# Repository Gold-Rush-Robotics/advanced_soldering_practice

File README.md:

# advanced_soldering_practice
Advanced Soldering Practice PCB

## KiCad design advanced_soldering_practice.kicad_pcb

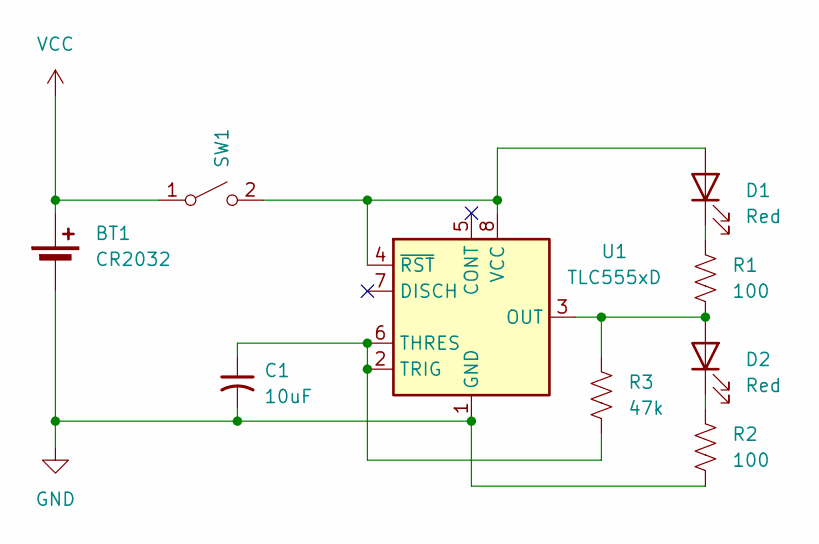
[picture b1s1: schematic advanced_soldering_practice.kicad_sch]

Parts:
BT1: CR2032; BAT-HLD-001-THM_TEC
C1: 10uF; C_0805_2012Metric_Pad1.18x1.45mm_HandSolder
D1, D2: Red; LED_0603_1608Metric_Pad1.05x0.95mm_HandSolder
R1, R2: 100; R_2010_5025Metric_Pad1.40x2.65mm_HandSolder
R3: 47k; R_0805_2012Metric_Pad1.20x1.40mm_HandSolder
SW1: SW_SPST; SW_PUSH_6mm_H5mm
U1: TLC555xD; SOIC-8_3.9x4.9mm_P1.27mm

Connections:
GND: BT1.2 (-), C1.2, R2.2, U1.1 (GND)
unnamed: D1.2 (A), SW1.2 (B), U1.4 (~RST), U1.8 (VCC)
unnamed: D1.1 (K), R1.1
unnamed: D2.2 (A), R1.2, R3.1, U1.3 (OUT)
unnamed: D2.1 (K), R2.1
unnamed: C1.1, R3.2, U1.2 (TRIG), U1.6 (THRES)
VCC: BT1.1 (+), SW1.1 (A)

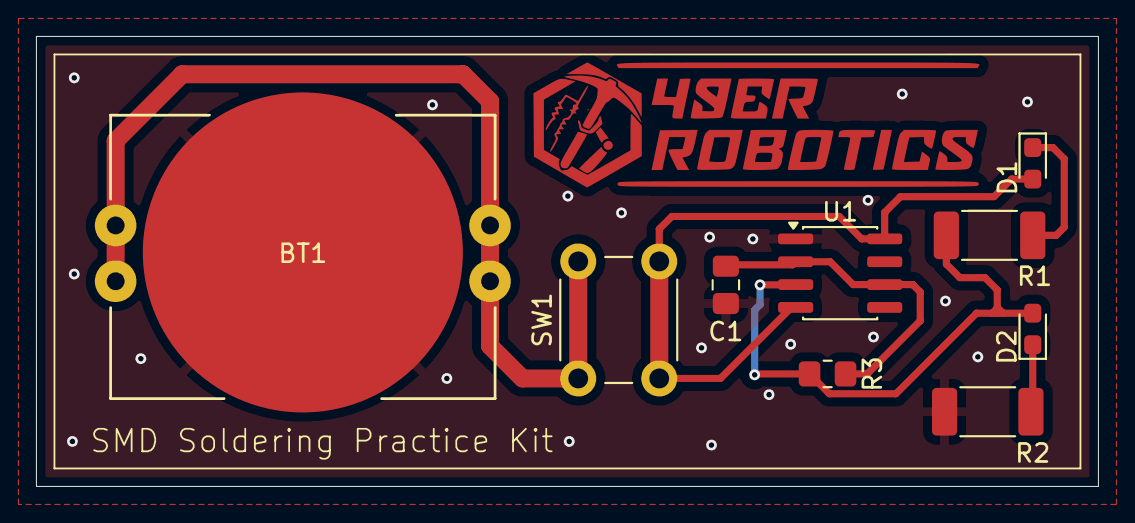
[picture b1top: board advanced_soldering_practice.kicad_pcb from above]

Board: 2 copper layers, 59.0 x 25.0 mm, 9 parts (0 on the bottom side), 7 nets.

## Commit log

2025-11-26 did simulation
2026-01-18 made advaned soldering practice
